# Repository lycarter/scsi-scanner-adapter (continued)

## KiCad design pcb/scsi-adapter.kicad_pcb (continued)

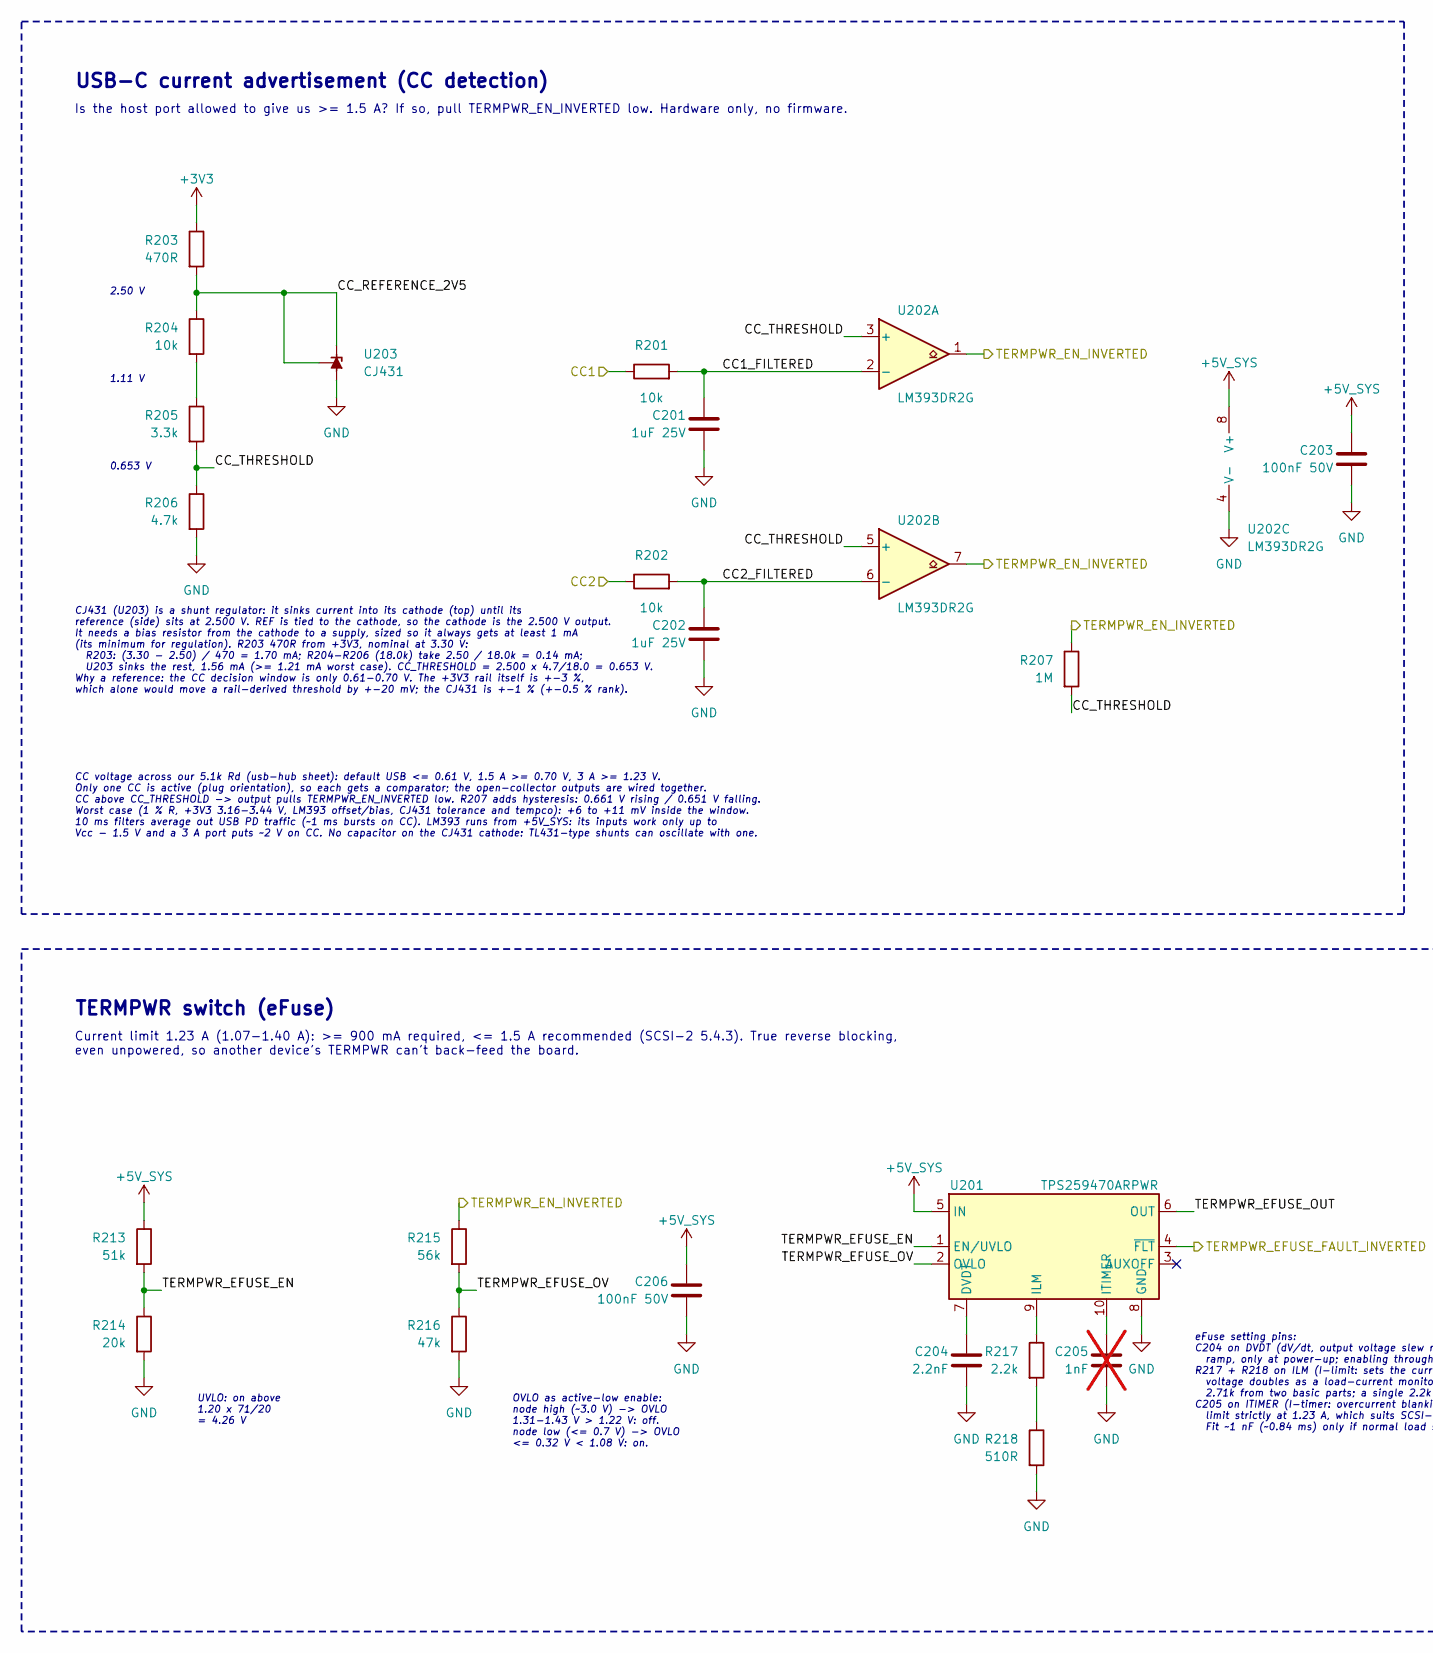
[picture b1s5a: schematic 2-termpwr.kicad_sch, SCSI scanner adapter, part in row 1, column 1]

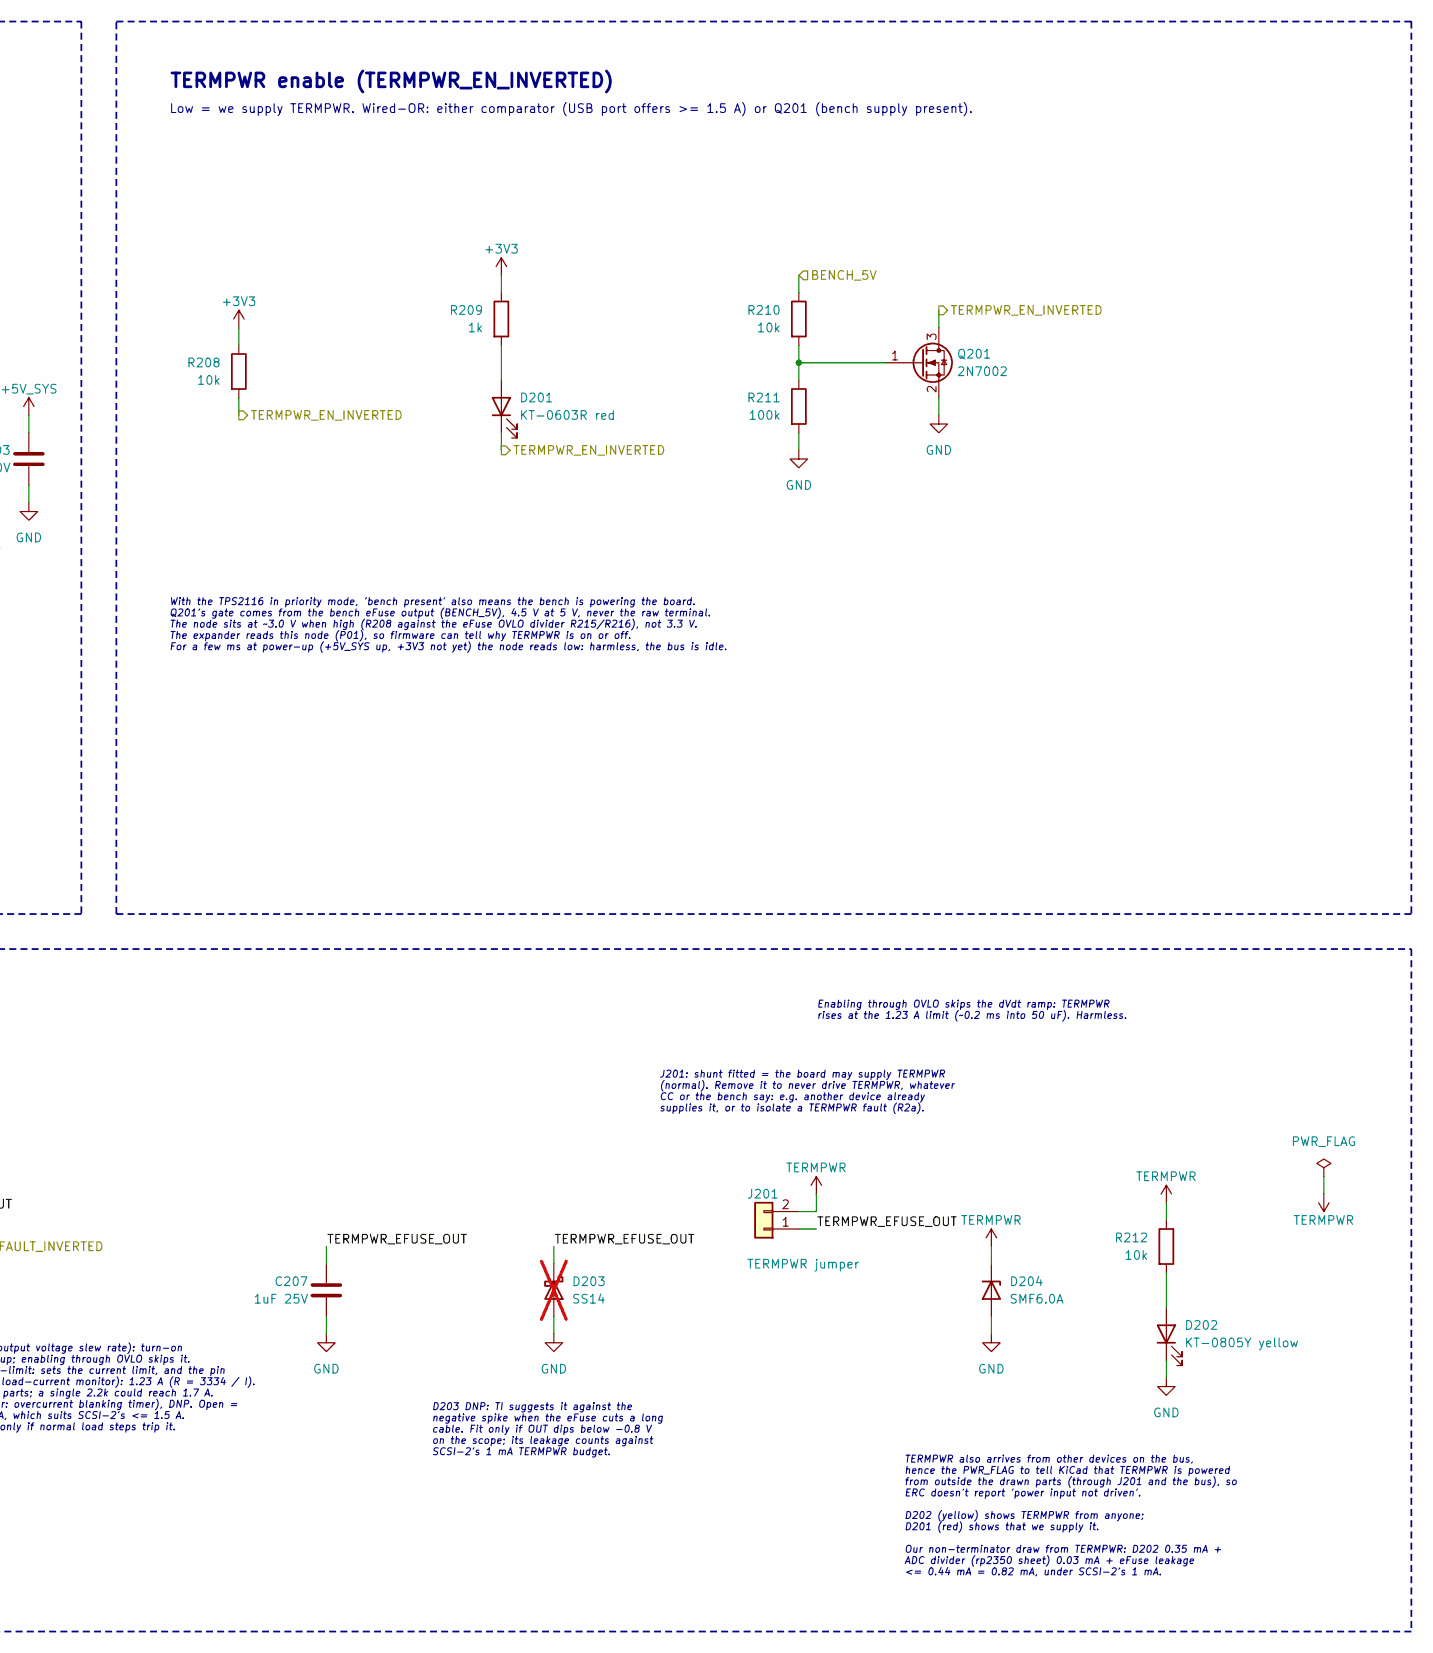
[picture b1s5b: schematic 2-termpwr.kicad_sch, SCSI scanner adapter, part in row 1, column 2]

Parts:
C201, C202, C207: 1uF 25V; C_0402_1005Metric; LCSC C52923
C203, C206: 100nF 50V; C_0402_1005Metric; LCSC C307331
C204: 2.2nF; C_0603_1608Metric; LCSC C1604
C205: 1nF; C_0402_1005Metric; not fitted
D201: KT-0603R red; LED_0603_1608Metric; LCSC C2286
D202: KT-0805Y yellow; LED_0805_2012Metric; LCSC C2296
D203: SS14; D_SMA; LCSC C2480; not fitted
D204: SMF6.0A; D_SOD-123F; LCSC C19077499
J201: TERMPWR jumper; PinHeader_1x02_P2.54mm_Vertical
Q201: 2N7002; SOT-23; LCSC C8545
R201, R202, R204, R208, R210, R212: 10k; R_0402_1005Metric; LCSC C25744
R203: 470R; R_0402_1005Metric; LCSC C25117
R205: 3.3k; R_0402_1005Metric; LCSC C25890
R206: 4.7k; R_0402_1005Metric; LCSC C25900
R207: 1M; R_0402_1005Metric; LCSC C26083
R209: 1k; R_0402_1005Metric; LCSC C11702
R211: 100k; R_0402_1005Metric; LCSC C25741
R213: 51k; R_0402_1005Metric; LCSC C25794
R214: 20k; R_0402_1005Metric; LCSC C25765
R215: 56k; R_0603_1608Metric; LCSC C23206
R216: 47k; R_0402_1005Metric; LCSC C25792
R217: 2.2k; R_0402_1005Metric; LCSC C25879
R218: 510R; R_0402_1005Metric; LCSC C25123
U201: TPS259470ARPWR; Texas_RPW0010A_VQFN-HR-10_2x2mm_P0.45mm; LCSC C3662799
U202: LM393DR2G; SOIC-8_3.9x4.9mm_P1.27mm; LCSC C7955
U203: CJ431; SOT-23; LCSC C3113

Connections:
+3V3: R203.1, R208.1, R209.1; also elsewhere on the board
+5V_SYS: C203.1, C206.1, R213.1, U201.5 (IN), U202.8 (V+); also elsewhere on the board
/BENCH_5V: R210.1; also elsewhere on the board
/CC1: R201.1; also elsewhere on the board
/CC2: R202.1; also elsewhere on the board
/TERMPWR_EFUSE_FAULT_INVERTED: U201.4 (~FLT); also elsewhere on the board
/TERMPWR_EN_INVERTED: D201.1 (K), Q201.3 (D), R207.1, R208.2, R215.1, U202.1, U202.7; also elsewhere on the board
/termpwr/CC1_FILTERED: C201.1, R201.2, U202.2 (-)
/termpwr/CC2_FILTERED: C202.1, R202.2, U202.6 (-)
/termpwr/CC_REFERENCE_2V5: R203.2, R204.1, U203.1 (REF), U203.2 (K)
/termpwr/CC_THRESHOLD: R205.2, R206.1, R207.2, U202.3 (+), U202.5 (+)
/termpwr/TERMPWR_EFUSE_EN: R213.2, R214.1, U201.1 (EN/UVLO)
/termpwr/TERMPWR_EFUSE_OUT: C207.1, D203.1 (K), J201.1, U201.6 (OUT)
/termpwr/TERMPWR_EFUSE_OV: R215.2, R216.1, U201.2 (OVLO)
GND: C201.2, C202.2, C203.2, C204.2, C205.2, C206.2, C207.2, D202.1 (K), D203.2 (A), D204.2 (A), Q201.2 (S), R206.2, R211.2, R214.2, R216.2, R218.2, U201.8 (GND), U202.4 (V-), U203.3 (A); also elsewhere on the board
unnamed: D201.2 (A), R209.2
unnamed: D202.2 (A), R212.2
unnamed: Q201.1 (G), R210.2, R211.1
unnamed: R204.2, R205.1
unnamed: R217.2, R218.1
unnamed: C204.1, U201.7 (DVDT)
unnamed: R217.1, U201.9 (ILM)
unnamed: C205.1, U201.10 (ITIMER)
TERMPWR: D204.1 (K), J201.2, R212.1; also elsewhere on the board

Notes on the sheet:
With the TPS2116 in priority mode, 'bench present' also means the bench is powering the board. Q201's gate comes from the bench eFuse output (BENCH_5V), 4.5 V at 5 V, never the raw terminal. The node sits at ~3.0 V when high (R208 against the eFuse OVLO divider R215/R216), not 3.3 V. The expander r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
Current limit 1.23 A (1.07-1.40 A): >= 900 mA required, <= 1.5 A recommended (SCSI-2 5.4.3). True reverse blocking, even unpowered, so another device's TERMPWR can't back-feed the board.
Enabling through OVLO skips the dVdt ramp: TERMPWR rises at the 1.23 A limit (~0.2 ms into 50 uF). Harmless.
CC voltage across our 5.1k Rd (usb-hub sheet): default USB <= 0.61 V, 1.5 A >= 0.70 V, 3 A >= 1.23 V. Only one CC is active (plug orientation), so each gets a comparator; the open-collector outputs are wired together. CC above CC_THRESHOLD -> output pulls TERMPWR_EN_INVERTED low. R207 adds hysteres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
USB-C current advertisement (CC detection)
TERMPWR enable (TERMPWR_EN_INVERTED)
0.653 V
J201: shunt fitted = the board may supply TERMPWR (normal). Remove it to never drive TERMPWR, whatever CC or the bench say: e.g. another device already supplies it, or to isolate a TERMPWR fault (R2a).
CJ431 (U203) is a shunt regulator: it sinks current into its cathode (top) until its reference (side) sits at 2.500 V. REF is tied to the cathode, so the cathode is the 2.500 V output. It needs a bias resistor from the cathode to a supply, sized so it always gets at least 1 mA (its minimum for regu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
2.50 V
1.11 V
TERMPWR switch (eFuse)
UVLO: on above 1.20 x 71/20 = 4.26 V
eFuse setting pins: C204 on DVDT (dV/dt, output voltage slew rate): turn-on ramp, only at power-up; enabling through OVLO skips it. R217 + R218 on ILM (I-limit: sets the current limit, and the pin voltage doubles as a load-current monitor): 1.23 A (R = 3334 / I). 2.71k from two basic parts; a singl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
Is the host port allowed to give us >= 1.5 A? If so, pull TERMPWR_EN_INVERTED low. Hardware only, no firmware.
Low = we supply TERMPWR. Wired-OR: either comparator (USB port offers >= 1.5 A) or Q201 (bench supply present).
D203 DNP: TI suggests it against the negative spike when the eFuse cuts a long cable. Fit only if OUT dips below -0.8 V on the scope; its leakage counts against SCSI-2's 1 mA TERMPWR budget.
TERMPWR also arrives from other devices on the bus, hence the PWR_FLAG to tell KiCad that TERMPWR is powered from outside the drawn parts (through J201 and the bus), so ERC doesn't report 'power input not driven'. D202 (yellow) shows TERMPWR from anyone; D201 (red) shows that we supply it. Our non-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
OVLO as active-low enable: node high (~3.0 V) -> OVLO 1.31-1.43 V > 1.22 V: off. node low (<= 0.7 V) -> OVLO <= 0.32 V < 1.08 V: on.

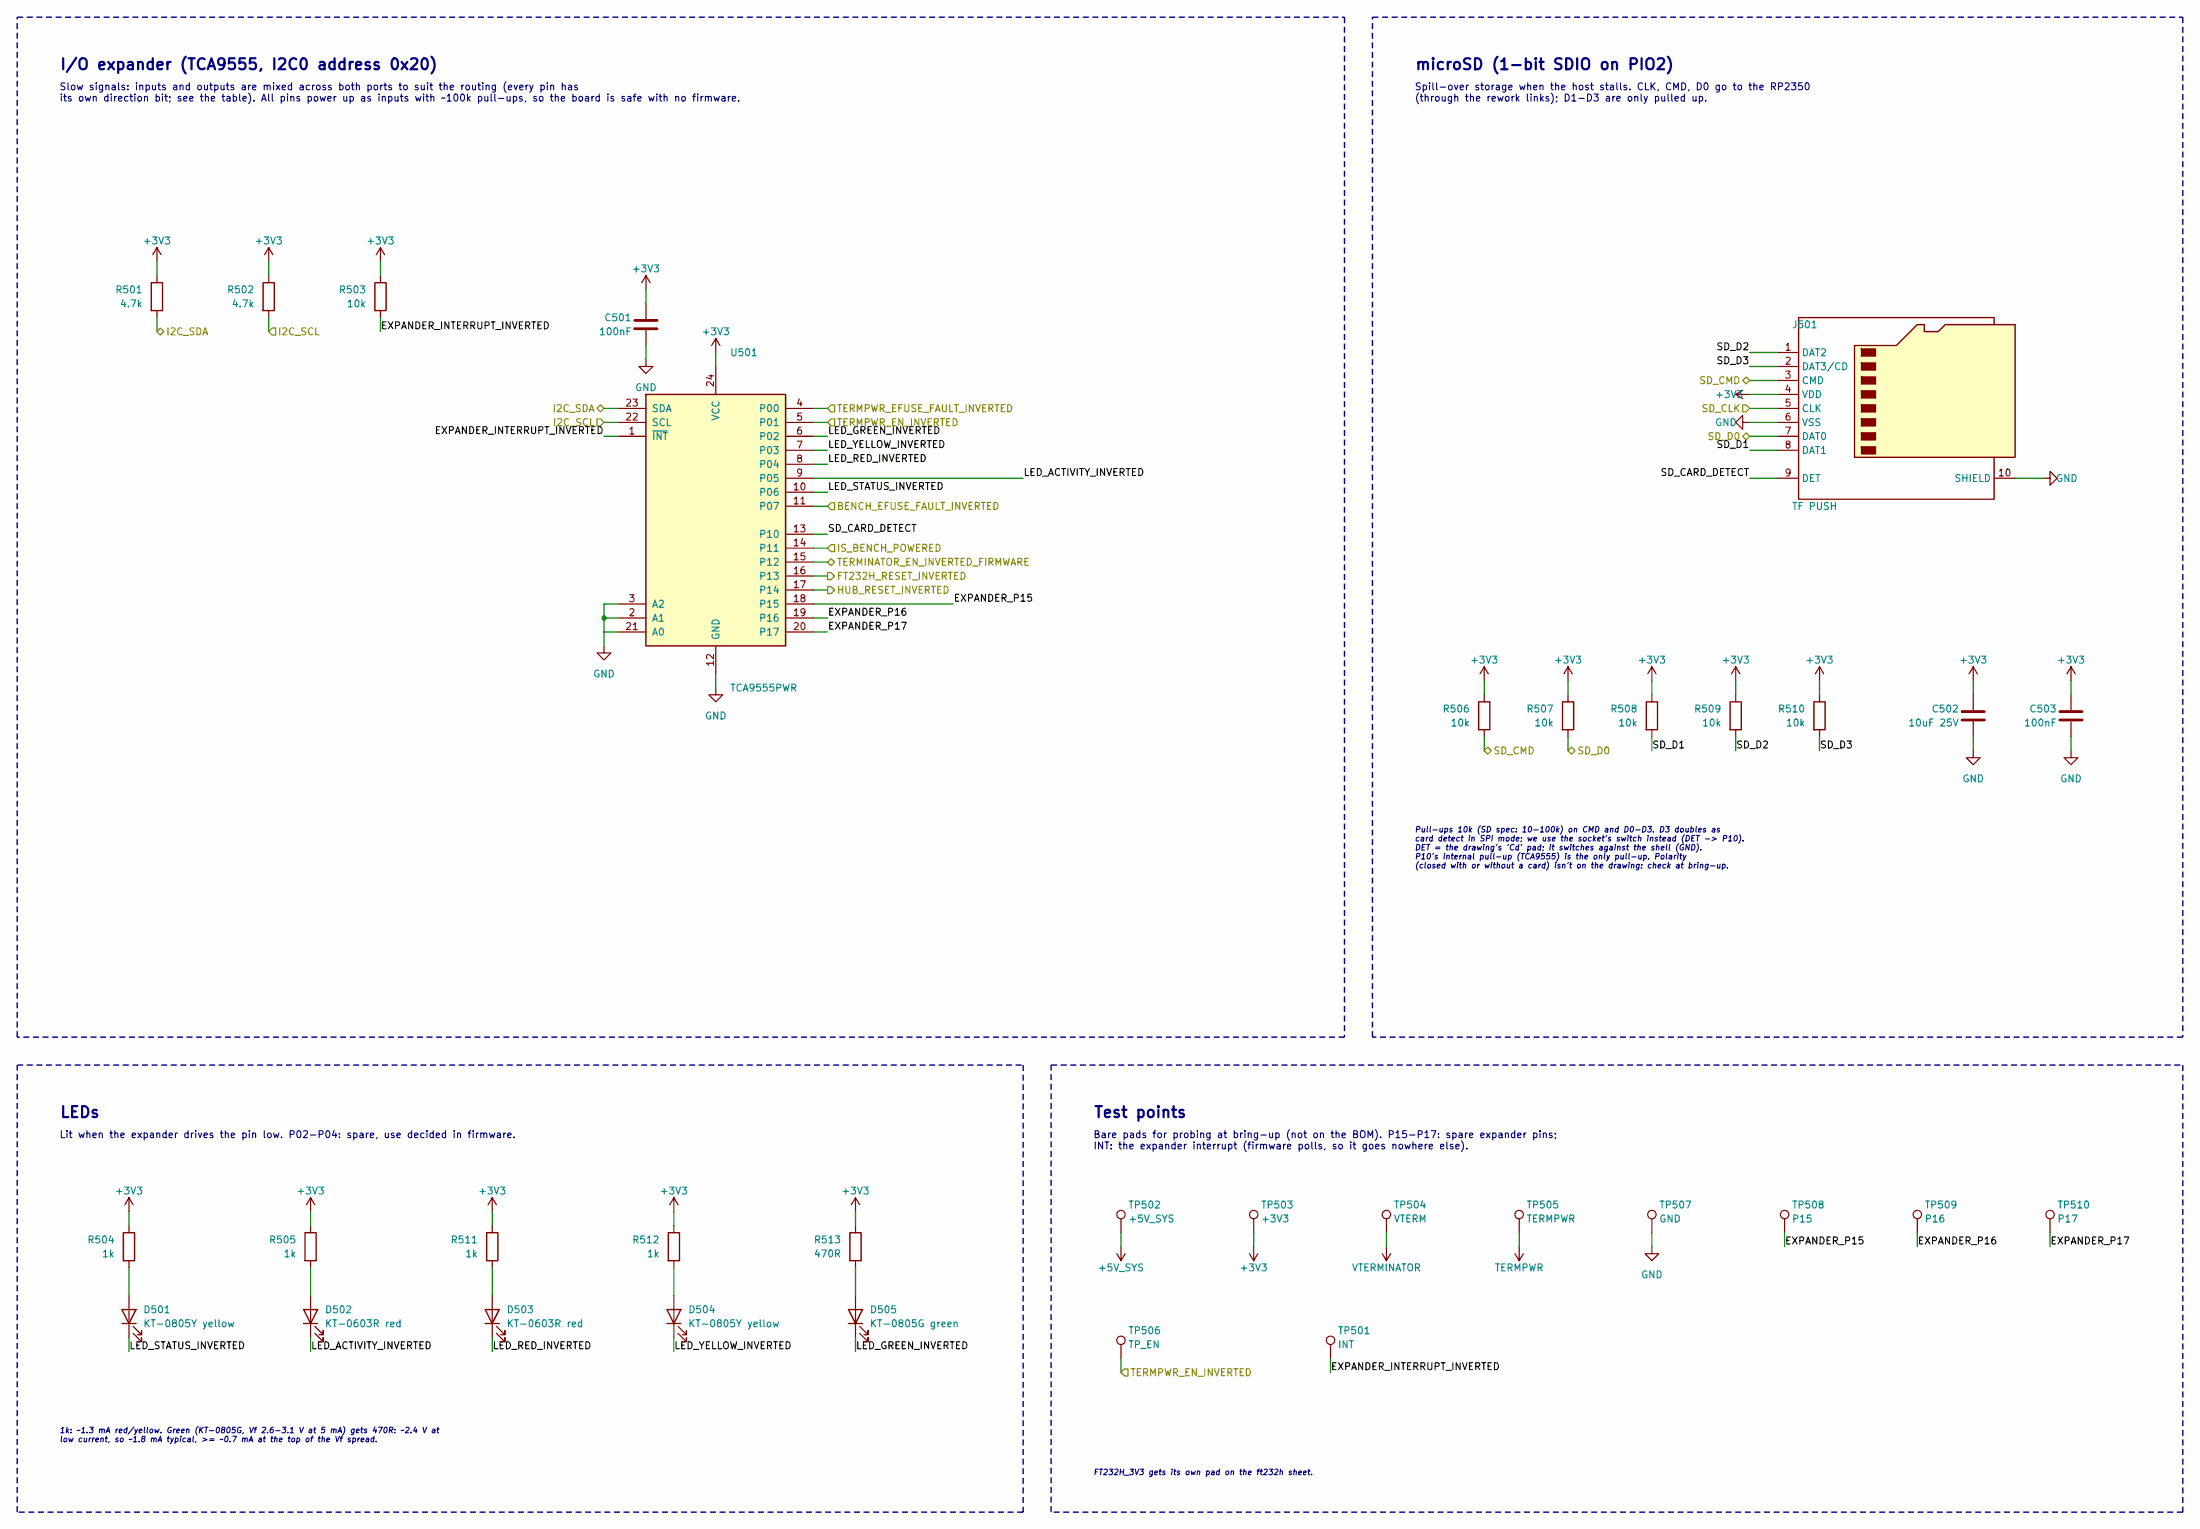
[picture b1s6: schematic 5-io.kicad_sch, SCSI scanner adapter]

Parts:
C501, C503: 100nF; C_0402_1005Metric; LCSC C307331
C502: 10uF 25V; C_0805_2012Metric; LCSC C15850
D501, D504: KT-0805Y yellow; LED_0805_2012Metric; LCSC C2296
D502, D503: KT-0603R red; LED_0603_1608Metric; LCSC C2286
D505: KT-0805G green; LED_0805_2012Metric; LCSC C2297
J501: TF PUSH; microSD_SHOUHAN_TF-PUSH_PushPush_CardDetect; LCSC C393941
R501, R502: 4.7k; R_0402_1005Metric; LCSC C25900
R503, R506, R507, R508, R509, R510: 10k; R_0402_1005Metric; LCSC C25744
R504, R505, R511, R512: 1k; R_0402_1005Metric; LCSC C11702
R513: 470R; R_0402_1005Metric; LCSC C25117
TP501: INT; TestPoint_Pad_D1.5mm
TP502: +5V_SYS; TestPoint_Pad_D1.5mm
TP503: +3V3; TestPoint_Pad_D1.5mm
TP504: VTERM; TestPoint_Pad_D1.5mm
TP505: TERMPWR; TestPoint_Pad_D1.5mm
TP506: TP_EN; TestPoint_Pad_D1.5mm
TP507: GND; TestPoint_Pad_D1.5mm
TP508: P15; TestPoint_Pad_D1.5mm
TP509: P16; TestPoint_Pad_D1.5mm
TP510: P17; TestPoint_Pad_D1.5mm
U501: TCA9555PWR; TSSOP-24_4.4x7.8mm_P0.65mm; LCSC C465732

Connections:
+3V3: C501.1, C502.1, C503.1, J501.4 (VDD), R501.1, R502.1, R503.1, R504.1, R505.1, R506.1, R507.1, R508.1, R509.1, R510.1, R511.1, R512.1, R513.1, TP503.1, U501.24 (VCC); also elsewhere on the board
/BENCH_EFUSE_FAULT_INVERTED: U501.11 (P07); also elsewhere on the board
/FT232H_RESET_INVERTED: U501.16 (P13); also elsewhere on the board
/HUB_RESET_INVERTED: U501.17 (P14); also elsewhere on the board
/I2C_SCL: R502.2, U501.22 (SCL); also elsewhere on the board
/I2C_SDA: R501.2, U501.23 (SDA); also elsewhere on the board
/IS_BENCH_POWERED: U501.14 (P11); also elsewhere on the board
/SD_CLK: J501.5 (CLK); also elsewhere on the board
/SD_CMD: J501.3 (CMD), R506.2; also elsewhere on the board
/SD_D0: J501.7 (DAT0), R507.2; also elsewhere on the board
/TERMINATOR_EN_INVERTED_FIRMWARE: U501.15 (P12); also elsewhere on the board
/TERMPWR_EFUSE_FAULT_INVERTED: U501.4 (P00); also elsewhere on the board
/TERMPWR_EN_INVERTED: TP506.1, U501.5 (P01); also elsewhere on the board
/io/EXPANDER_INTERRUPT_INVERTED: R503.2, TP501.1, U501.1 (~INT); also elsewhere on the board
/io/EXPANDER_P15: TP508.1, U501.18 (P15); also elsewhere on the board
/io/EXPANDER_P16: TP509.1, U501.19 (P16); also elsewhere on the board
/io/EXPANDER_P17: TP510.1, U501.20 (P17); also elsewhere on the board
/io/LED_ACTIVITY_INVERTED: D502.1 (K), U501.9 (P05)
/io/LED_GREEN_INVERTED: D505.1 (K), U501.6 (P02)
/io/LED_RED_INVERTED: D503.1 (K), U501.8 (P04)
/io/LED_STATUS_INVERTED: D501.1 (K), U501.10 (P06)
/io/LED_YELLOW_INVERTED: D504.1 (K), U501.7 (P03)
/io/SD_CARD_DETECT: J501.9 (DET), U501.13 (P10)
/io/SD_D1: J501.8 (DAT1), R508.2
/io/SD_D2: J501.1 (DAT2), R509.2
/io/SD_D3: J501.2 (DAT3/CD), R510.2
GND: C501.2, C502.2, C503.2, J501.6 (VSS), J501.10 (SHIELD), TP507.1, U501.2 (A1), U501.3 (A2), U501.12 (GND), U501.21 (A0); also elsewhere on the board
unnamed: D501.2 (A), R504.2
unnamed: D502.2 (A), R505.2
unnamed: D503.2 (A), R511.2
unnamed: D504.2 (A), R512.2
unnamed: D505.2 (A), R513.2

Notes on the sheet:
I/O expander (TCA9555, I2C0 address 0x20)
Test points
LEDs
Bare pads for probing at bring-up (not on the BOM). P15-P17: spare expander pins; INT: the expander interrupt (firmware polls, so it goes nowhere else).
Pull-ups 10k (SD spec: 10-100k) on CMD and D0-D3. D3 doubles as card detect in SPI mode; we use the socket's switch instead (DET -> P10). DET = the drawing's 'Cd' pad; it switches against the shell (GND). P10's internal pull-up (TCA9555) is the only pull-up. Polarity (closed with or without a card)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
Slow signals: inputs and outputs are mixed across both ports to suit the routing (every pin has its own direction bit; see the table). All pins power up as inputs with ~100k pull-ups, so the board is safe with no firmware.
microSD (1-bit SDIO on PIO2)
Spill-over storage when the host stalls. CLK, CMD, D0 go to the RP2350 (through the rework links); D1-D3 are only pulled up.
1k: ~1.3 mA red/yellow. Green (KT-0805G, Vf 2.6-3.1 V at 5 mA) gets 470R: ~2.4 V at low current, so ~1.8 mA typical, >= ~0.7 mA at the top of the Vf spread.
FT232H_3V3 gets its own pad on the ft232h sheet.
Lit when the expander drives the pin low. P02-P04: spare, use decided in firmware.

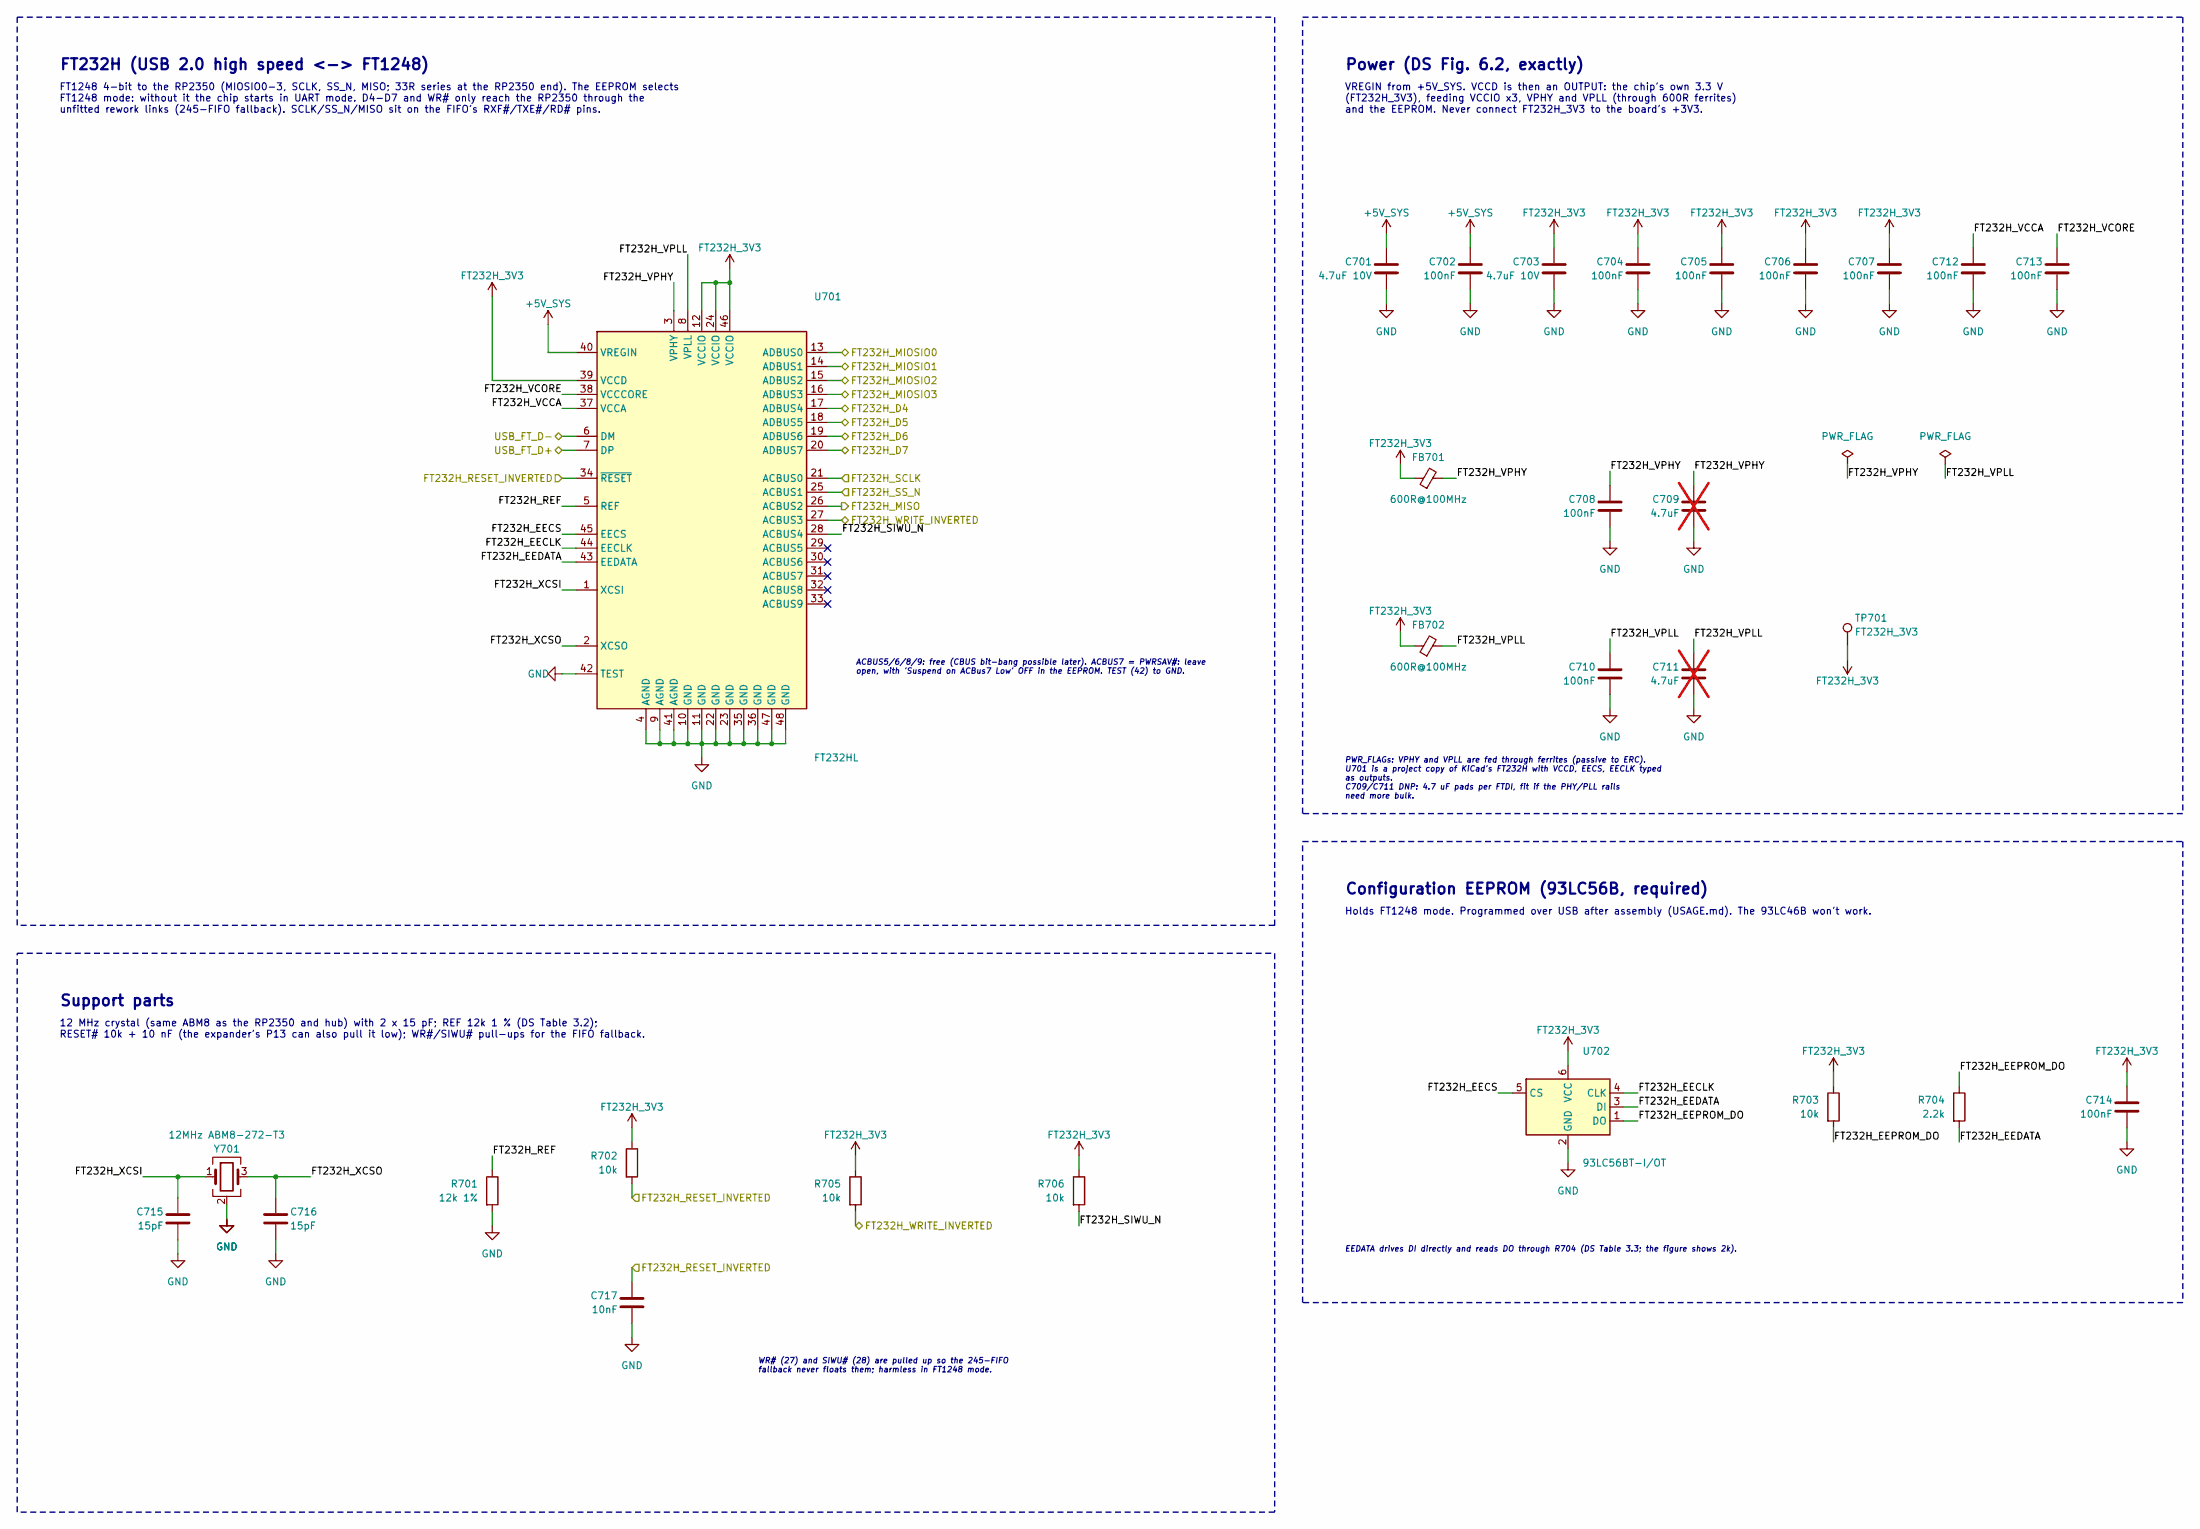
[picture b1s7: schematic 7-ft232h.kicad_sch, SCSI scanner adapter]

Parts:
C701, C703: 4.7uF 10V; C_0402_1005Metric; LCSC C23733
C702, C704, C705, C706, C707, C708, C710, C712, C713, C714: 100nF; C_0402_1005Metric; LCSC C307331
C709, C711: 4.7uF; C_0402_1005Metric; LCSC C23733; not fitted
C715, C716: 15pF; C_0402_1005Metric; LCSC C1548
C717: 10nF; C_0402_1005Metric; LCSC C15195
FB701, FB702: 600R@100MHz; L_0603_1608Metric; LCSC C1002
R701: 12k 1%; R_0402_1005Metric; LCSC C25752
R702, R703, R705, R706: 10k; R_0402_1005Metric; LCSC C25744
R704: 2.2k; R_0402_1005Metric; LCSC C25879
TP701: FT232H_3V3; TestPoint_Pad_D1.5mm
U701: FT232HL; LQFP-48_7x7mm_P0.5mm; LCSC C51997
U702: 93LC56BT-I/OT; SOT-23-6; LCSC C190271
Y701: 12MHz ABM8-272-T3; Crystal_SMD_3225-4Pin_3.2x2.5mm; LCSC C20625731

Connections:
+5V_SYS: C701.1, C702.1, U701.40 (VREGIN); also elsewhere on the board
/FT232H_D4: U701.17 (ADBUS4); also elsewhere on the board
/FT232H_D5: U701.18 (ADBUS5); also elsewhere on the board
/FT232H_D6: U701.19 (ADBUS6); also elsewhere on the board
/FT232H_D7: U701.20 (ADBUS7); also elsewhere on the board
/FT232H_MIOSIO0: U701.13 (ADBUS0); also elsewhere on the board
/FT232H_MIOSIO1: U701.14 (ADBUS1); also elsewhere on the board
/FT232H_MIOSIO2: U701.15 (ADBUS2); also elsewhere on the board
/FT232H_MIOSIO3: U701.16 (ADBUS3); also elsewhere on the board
/FT232H_MISO: U701.26 (ACBUS2); also elsewhere on the board
/FT232H_RESET_INVERTED: C717.1, R702.2, U701.34 (~RESET); also elsewhere on the board
/FT232H_SCLK: U701.21 (ACBUS0); also elsewhere on the board
/FT232H_SS_N: U701.25 (ACBUS1); also elsewhere on the board
/FT232H_WRITE_INVERTED: R705.2, U701.27 (ACBUS3); also elsewhere on the board
/USB_FT_D+: U701.7 (DP); also elsewhere on the board
/USB_FT_D-: U701.6 (DM); also elsewhere on the board
/ft232h/FT232H_EECLK: U701.44 (EECLK), U702.4 (CLK)
/ft232h/FT232H_EECS: U701.45 (EECS), U702.5 (CS)
/ft232h/FT232H_EEDATA: R704.2, U701.43 (EEDATA), U702.3 (DI)
/ft232h/FT232H_EEPROM_DO: R703.2, R704.1, U702.1 (DO)
/ft232h/FT232H_REF: R701.1, U701.5 (REF)
/ft232h/FT232H_SIWU_N: R706.2, U701.28 (ACBUS4)
/ft232h/FT232H_VCCA: C712.1, U701.37 (VCCA)
/ft232h/FT232H_VCORE: C713.1, U701.38 (VCCCORE)
/ft232h/FT232H_VPHY: C708.1, C709.1, FB701.2, U701.3 (VPHY)
/ft232h/FT232H_VPLL: C710.1, C711.1, FB702.2, U701.8 (VPLL)
/ft232h/FT232H_XCSI: C715.1, U701.1 (XCSI), Y701.1
/ft232h/FT232H_XCSO: C716.1, U701.2 (XCSO), Y701.3
FT232H_3V3: C703.1, C704.1, C705.1, C706.1, C707.1, C714.1, FB701.1, FB702.1, R702.1, R703.1, R705.1, R706.1, TP701.1, U701.12 (VCCIO), U701.24 (VCCIO), U701.39 (VCCD), U701.46 (VCCIO), U702.6 (VCC); also elsewhere on the board
GND: C701.2, C702.2, C703.2, C704.2, C705.2, C706.2, C707.2, C708.2, C709.2, C710.2, C711.2, C712.2, C713.2, C714.2, C715.2, C716.2, C717.2, R701.2, U701.4 (AGND), U701.9 (AGND), U701.10 (GND), U701.11 (GND), U701.22 (GND), U701.23 (GND), U701.35 (GND), U701.36 (GND), U701.41 (AGND), U701.42 (TEST), U701.47 (GND), U701.48 (GND), U702.2 (GND), Y701.2 (G), Y701.4 (G); also elsewhere on the board

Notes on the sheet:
Holds FT1248 mode. Programmed over USB after assembly (USAGE.md). The 93LC46B won't work.
WR# (27) and SIWU# (28) are pulled up so the 245-FIFO fallback never floats them; harmless in FT1248 mode.
VREGIN from +5V_SYS. VCCD is then an OUTPUT: the chip's own 3.3 V (FT232H_3V3), feeding VCCIO x3, VPHY and VPLL (through 600R ferrites) and the EEPROM. Never connect FT232H_3V3 to the board's +3V3.
PWR_FLAGs: VPHY and VPLL are fed through ferrites (passive to ERC). U701 is a project copy of KiCad's FT232H with VCCD, EECS, EECLK typed as outputs. C709/C711 DNP: 4.7 uF pads per FTDI, fit if the PHY/PLL rails need more bulk.
12 MHz crystal (same ABM8 as the RP2350 and hub) with 2 x 15 pF; REF 12k 1 % (DS Table 3.2); RESET# 10k + 10 nF (the expander's P13 can also pull it low); WR#/SIWU# pull-ups for the FIFO fallback.
Support parts
FT1248 4-bit to the RP2350 (MIOSIO0-3, SCLK, SS_N, MISO; 33R series at the RP2350 end). The EEPROM selects FT1248 mode: without it the chip starts in UART mode. D4-D7 and WR# only reach the RP2350 through the unfitted rework links (245-FIFO fallback). SCLK/SS_N/MISO sit on the FIFO's RXF#/TXE#/RD# 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
EEDATA drives DI directly and reads DO through R704 (DS Table 3.3; the figure shows 2k).
FT232H (USB 2.0 high speed <-> FT1248)
ACBUS5/6/8/9: free (CBUS bit-bang possible later). ACBUS7 = PWRSAV#: leave open, with 'Suspend on ACBus7 Low' OFF in the EEPROM. TEST (42) to GND.
Power (DS Fig. 6.2, exactly)
Configuration EEPROM (93LC56B, required)
